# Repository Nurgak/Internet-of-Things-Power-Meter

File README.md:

# Internet-of-Things Power Meter

The Internet-of-Things Power Meter (IPM) is a device fixed on top of the regular household power meter and provides detailed information about the electricity usage. Modern power meters have a LED blinking every time a Watt is used, the IPM detects these flashes using a light sensor, counts them and saves the values to an SD card. Later the data is stored on the cloud.

Usually power companies provide very rough electricity usage data, the IPM provides data with a minute resolution. Knowing the household electricity usage allows to extrapolate statistics and can give precise numbers about the costs.

The IPM was made with simplicity of assembly and cost in mind. The device is easy to build, program and cheap to deploy and use. One can basically buy the parts, assemble, program and deploy it without any knowledge about the inner workings, however contribution to the development of this open-source project is welcome and encouraged.

This is the second iteration of the electricity usage monitor project, the [first version can be seen here](https://github.com/Nurgak/Electricity-usage-monitor).

# Documentation

During development the IPM project is [documented on hackaday.io](https://hackaday.io/project/6938-internet-of-things-power-meter).

# License

The software is licensed under [GNU General Public License](https://en.wikipedia.org/wiki/GNU_General_Public_License).

The hardware is licensed under [Creative Commons Attribution-ShareAlike 4.0 International License](http://creativecommons.org/licenses/by-sa/4.0/).

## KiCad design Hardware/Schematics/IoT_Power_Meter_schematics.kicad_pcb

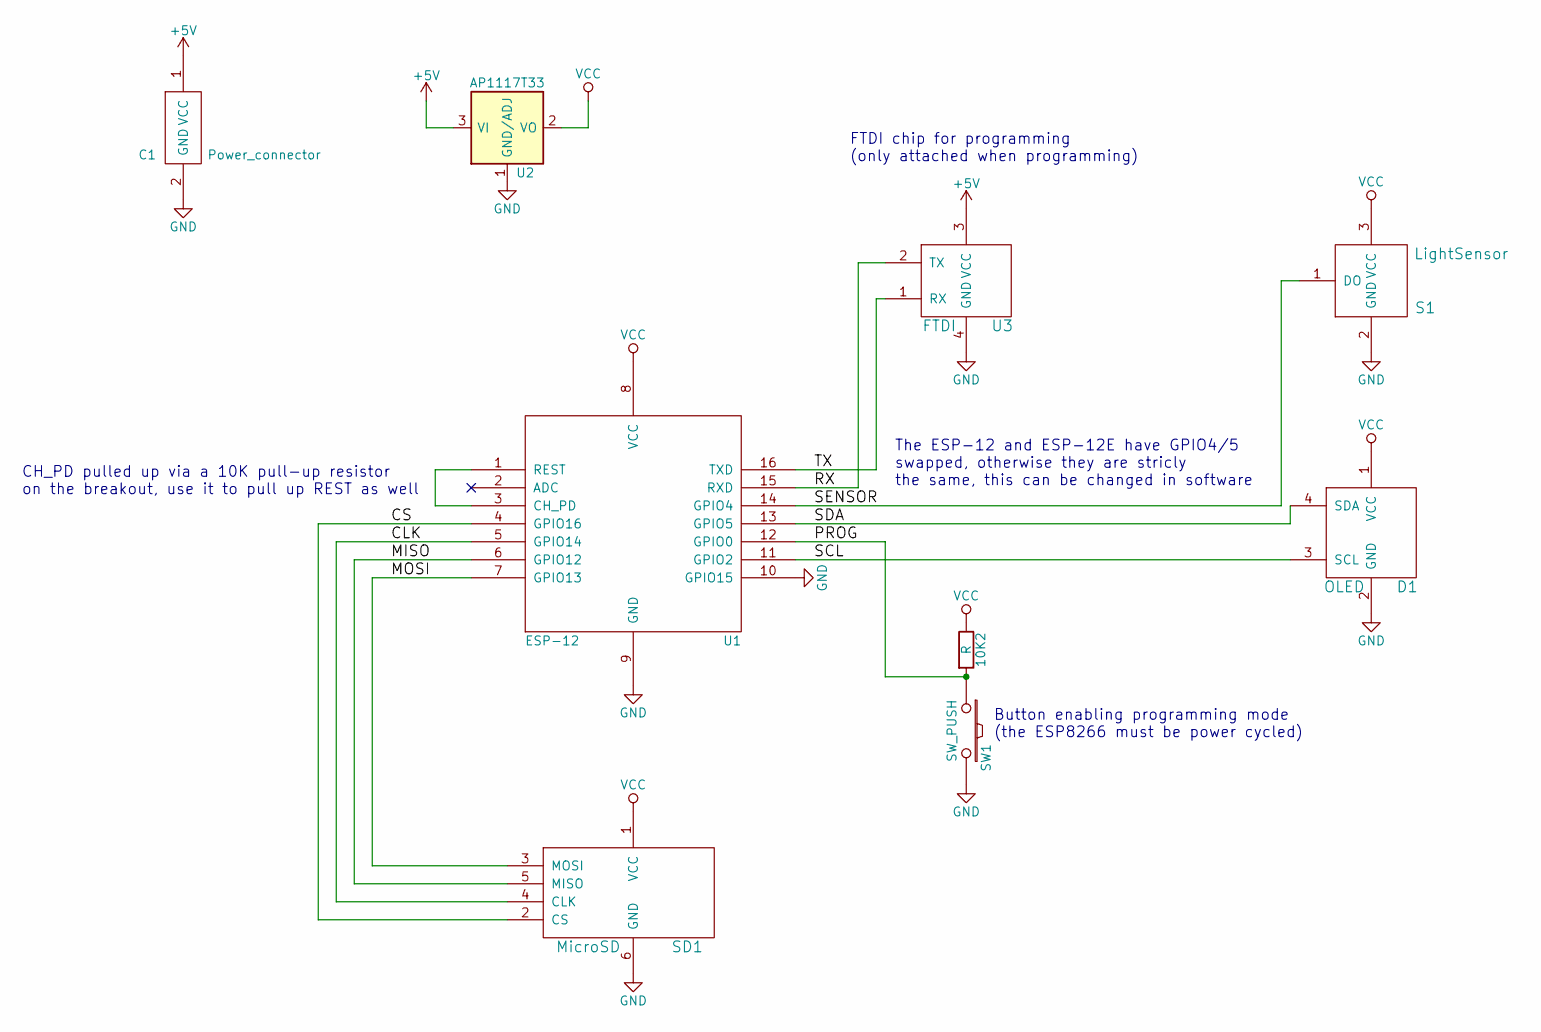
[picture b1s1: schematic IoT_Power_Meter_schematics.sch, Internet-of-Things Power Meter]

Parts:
10K2: R; Resistor_Horizontal_RM10mm
C1: Power_connector
D1: OLED
S1: LightSensor
SD1: MicroSD; uSD_card_reader
SW1: SW_PUSH; Button
U1: ESP-12; ESP8266-12E_breakout
U2: AP1117T33; 5-3V3_LDO
U3: FTDI

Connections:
+5V: C1.1 (VCC), U2.3 (VI), U3.3 (VCC)
/CLK: SD1.4 (CLK), U1.5 (GPIO14)
/CS: SD1.2 (CS), U1.4 (GPIO16)
/MISO: SD1.5 (MISO), U1.6 (GPIO12)
/MOSI: SD1.3 (MOSI), U1.7 (GPIO13)
/PROG: 10K2.2, SW1.1, U1.12 (GPIO0)
/RX: U1.15 (RXD), U3.2 (TX)
/SCL: D1.3 (SCL), U1.11 (GPIO2)
/SDA: D1.4 (SDA), U1.13 (GPIO5)
/SENSOR: S1.1 (DO), U1.14 (GPIO4)
/TX: U1.16 (TXD), U3.1 (RX)
GND: C1.2 (GND), D1.2 (GND), S1.2 (GND), SD1.6 (GND), SW1.2, U1.9 (GND), U1.10 (GPIO15), U2.1 (GND/ADJ), U3.4 (GND)
unnamed: U1.1 (REST), U1.3 (CH_PD)
VCC: 10K2.1, D1.1 (VCC), S1.3 (VCC), SD1.1 (VCC), U1.8 (VCC), U2.2 (VO)

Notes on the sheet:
Button enabling programming mode (the ESP8266 must be power cycled)
FTDI chip for programming (only attached when programming)
CH_PD pulled up via a 10K pull-up resistor on the breakout, use it to pull up REST as well
The ESP-12 and ESP-12E have GPIO4/5 swapped, otherwise they are stricly the same, this can be changed in software

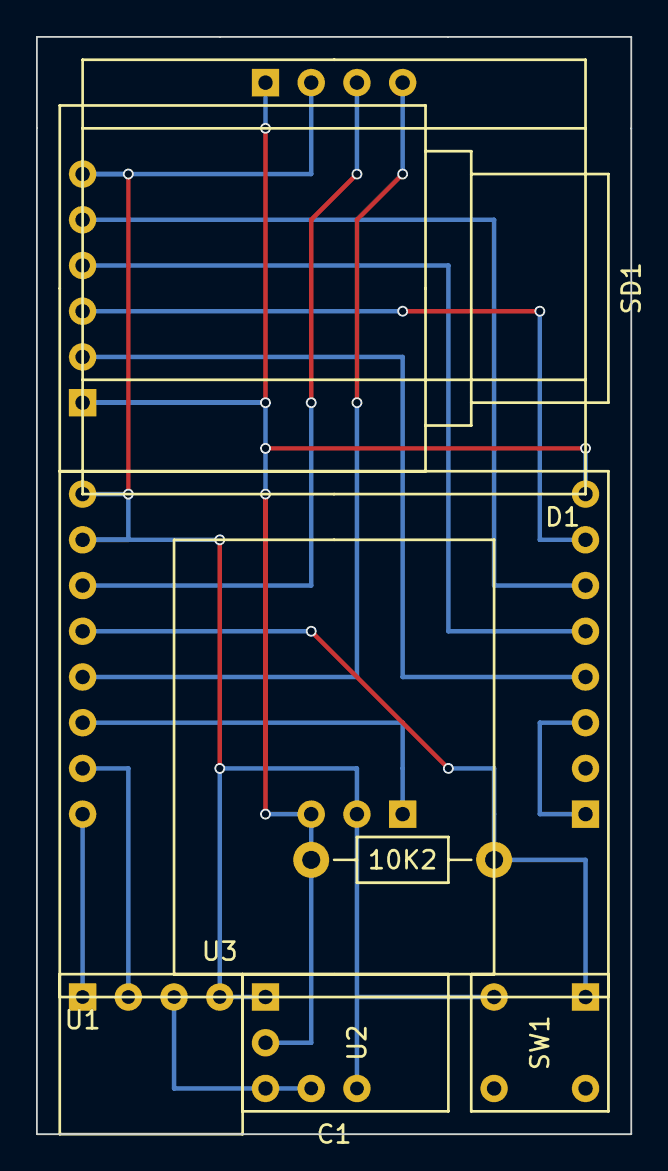
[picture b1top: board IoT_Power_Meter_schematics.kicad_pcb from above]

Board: 2 copper layers, 33.0 x 61.0 mm, 9 parts (1 on the bottom side), 14 nets.

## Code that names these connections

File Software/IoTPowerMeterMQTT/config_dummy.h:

/*
  IoTPowerMeter - Software for the IoTPowerMeter based on the ESP8266

  Copyright (c) 2016 Karl Kangur. All rights reserved.
  This file is part of IoTPowerMeter.

  IoTPowerMeter is free software: you can redistribute it and/or modify
  it under the terms of the GNU General Public License as published by
  the Free Software Foundation, either version 3 of the License, or
  (at your option) any later version.

  IoTPowerMeter is distributed in the hope that it will be useful,
  but WITHOUT ANY WARRANTY; without even the implied warranty of
  MERCHANTABILITY or FITNESS FOR A PARTICULAR PURPOSE.  See the
  GNU General Public License for more details.

  You should have received a copy of the GNU General Public License
  along with IoTPowerMeter.  If not, see <http://www.gnu.org/licenses/>.
*/

/*
 * File:    config_dummy.h
 * Author:  Karl Kangur <karl.kangur@gmail.com>
 * Licnece: GPL
 * URL:     https://github.com/Nurgak/Internet-of-Things-Power-Meter
 */

#ifndef CONFIG_H
#define CONFIG_H

/*** WARNING: ESP-12 and ESP-12E have their GPIO4/5 swapped, so define the correct pins here ***/

// Light sensor pin (do not use GPIO16, it cannot do interrupts)
#define SENSOR_PIN 5
// Button is used for entering programming mode or to toggle between functions (GPIO0)
#define BUTTON_PIN 0
// Chip select pin for the SD card reader
#define SD_CS_PIN 16
// Pin connected to the LED (serial TX)
#define LED_PIN 1
// I2C data and clock pins for the screen
#define PIN_SDA 4
#define PIN_SCL 2

// How often the internal time is synchronised with the NTP server
#define TIME_SYNC_PERIOD 12*60*60 // [s]
// NTP server from which to fetch the time
static const char * ntpServerName = "time.nist.gov";

#define ENABLE_INTERNET // Comment thus line to remove all internet related functionalities
static const char * wifi_ssid = "...";
static const char * wifi_password = "...";

// MQTT server configuration
static const char * mqtt_server = "192.168.1.3";
static const unsigned int mqtt_port = 1883;
static const char * hostName = "IoTPowerMeter";

// Global constants, no magic numbers
#define TIME_WIFI_CONNECT 5000 // Maximum waiting time in seconds for Wi-Fi connection
#define TIME_SYNC_RESPONSE 3000 // Maximum time the system will wait for a response from the NTP server (milliseconds)
#define TIME_BUTTON_PRESS_SHORT 100 // Time in milliseconds for the short button press routine to execute
#define TIME_BUTTON_PRESS_LONG 2000 // Time in milliseconds for the long button press routine to execute
#define TIME_DEBOUNCE 200 // Time in milliseconds during which LED blinks are ignored when one was just detected
#define SCREEN_TITLE_COLUMN 0 // Horizontal position from which the title should be displayed on screen
#define SCREEN_START_COLUMN 6 // Horizontal position from which the data should be displayed on screen
#define SCREEN_ROW_STAT  0
#define SCREEN_ROW_IP    1
#define SCREEN_ROW_DATE  2
#define SCREEN_ROW_TIME  3
#define SCREEN_ROW_NOW   4
#define SCREEN_ROW_TODAY 5
#define SCREEN_ROW_HEAP  6
#define NTP_PACKET_SIZE 48

// For debugging
/*#define DEBUG_SERIAL Serial
#define DEBUG_BAUDRATE 115200
#define DEBUGV(...) ets_printf(__VA_ARGS__)*/

#endif

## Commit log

2016-05-24 Added Google Spreadsheets uploading capability
2016-05-24 Removed debug output
2016-05-25 Removed some magic numbers, resized pictures, added logging to file capability
2016-05-26 Added token check, removed more magic numbers and updated Google scripts
2016-05-27 Added debounce routine, squished Google script bugs
2016-05-29 Changed units for the live consumption, should've been W not Wh. Uploaded pictures.
2016-06-25 Disabled Google Spreadsheet upload by default
2018-06-02 Added MQTT version
